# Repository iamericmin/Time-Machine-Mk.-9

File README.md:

# Time-Machine-Mk.-9
Time Machine Mk. 9

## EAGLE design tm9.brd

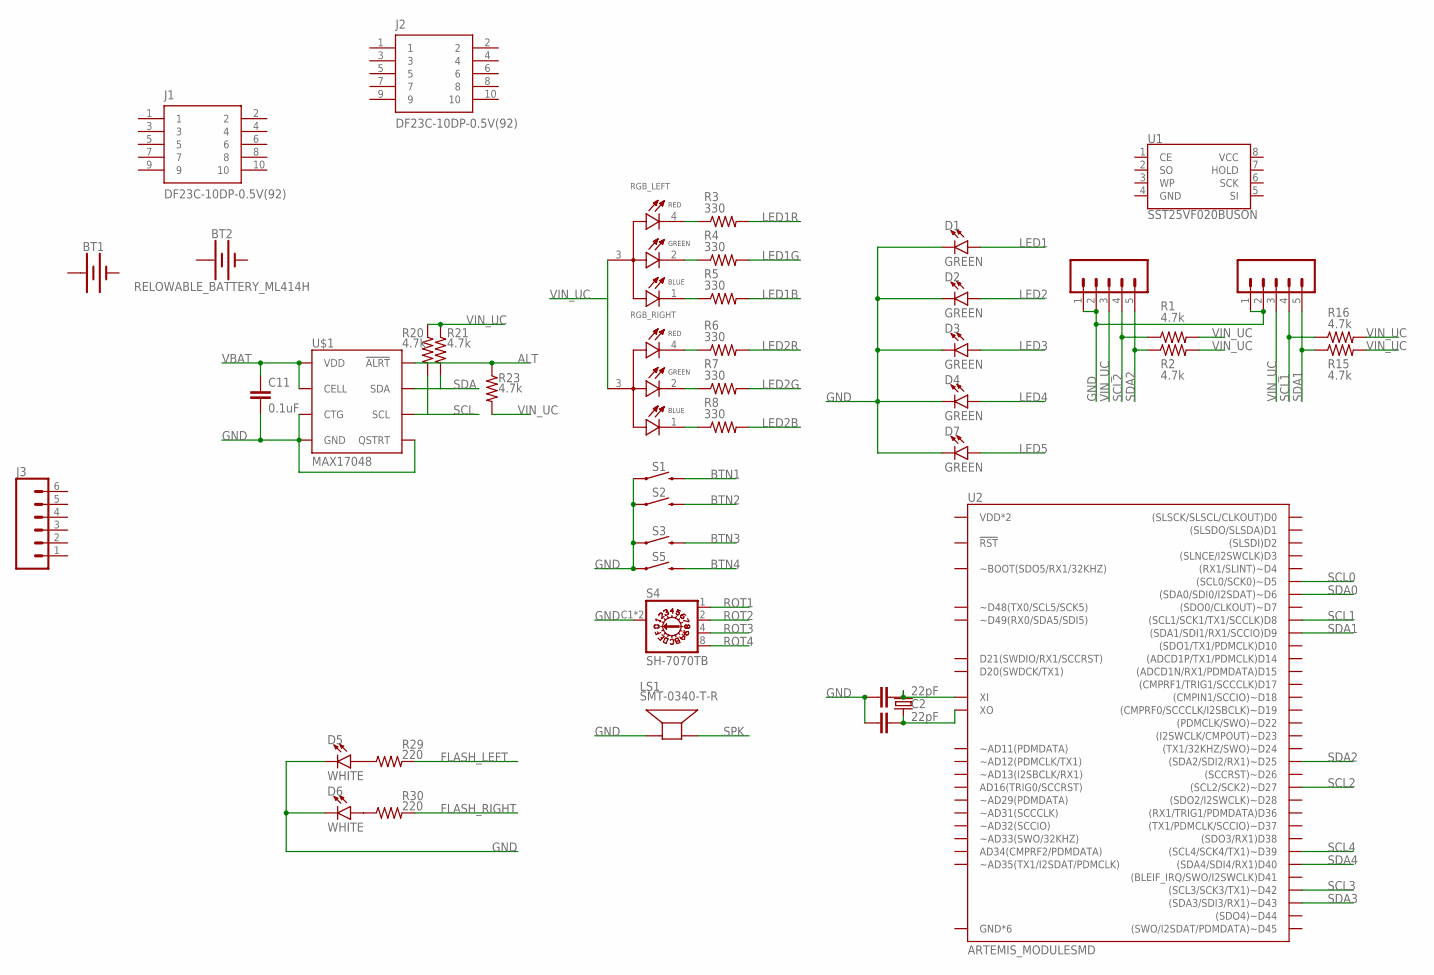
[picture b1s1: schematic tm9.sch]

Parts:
BT1: BATTERY-20MM_SMD_4LEGS_OVERPASTE_INNER; BATTCON_20MM_4LEGS_OVERPASTE_INNER
BT2: RELOWABLE_BATTERY_ML414H; ML414H_IV01E
C1, C2: 22pF; C0402
C11: 0.1uF; C0402
D1, D2, D3, D4, D7: GREEN; LED-1206
D5, D6: WHITE; LED-1206
J1, J2: DF23C-10DP-0.5V(92); HIROSE_DF23C-10DP-0.5V(92)
J3: CONN_06JST-SMD-LOCKING; JST-6-SMD-1.25MM-LOCKING
LCD1, LCD2: CONN_05VERT_FEMALE_HEADER; 1X05_SMD_VERTICAL_COMBO
LS1: SMT-0340-T-R; XDCR_SMT-0340-T-R
R1, R2, R15, R16, R20, R21, R23: 4.7k; R0402
R3, R4, R5, R6, R7, R8: 330; R0402
R29, R30: 220; R0402
RGB_LEFT: EAST1616RGBA3; LED_EAST1616RGBA3
RGB_RIGHT: EAST1616RGBA3; LED_EAST1616RGBA3
S1, S2, S3, S5: MOMENTARY-SWITCH-SPST-SMD-6.0X3.5MM; TACTILE_SWITCH_SMD_6.0X3.5MM
S4: SH-7070TB; SH-7070B
U1: SST25VF020BUSON; USON_3X2MM
U2: ARTEMIS_MODULESMD; ARTEMIS_FP
U$1: MAX17048; DFN-8
Y1: 32.768kHz; CRYSTAL-SMD-3.2X1.5MM

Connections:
+: BT1.1 (+), BT2.+
-: BT1.2 (-), BT2.-
ALT: R23.1, U$1.P$5 (!ALRT)
BTN1: S1.2
BTN2: S2.2
BTN3: S3.2
BTN4: S5.2
FLASH_LEFT: R29.2
FLASH_RIGHT: R30.2
GND: C1.1, C2.1, C11.2, D1.C, D2.C, D3.C, D4.C, D5.C, D6.C, D7.C, LCD1.1, LCD1.2, LCD2.1, LCD2.2, LS1.P, S1.1, S2.1, S3.1, S4.C1 (C), S4.C2 (C), S5.1, U1.4 (GND), U$1.P$1 (CTG), U$1.P$4 (GND), U$1.P$6 (QSTRT), U$1.P$9 (GND)
LED1: D1.A
LED1B: R5.2
LED1G: R4.2
LED1R: R3.2
LED2: D2.A
LED2B: R8.2
LED2G: R7.2
LED2R: R6.2
LED3: D3.A
LED4: D4.A
LED5: D7.A
unnamed: R3.1, RGB_LEFT.4 (R_C)
unnamed: R4.1, RGB_LEFT.2 (G_C)
unnamed: R5.1, RGB_LEFT.1 (B_C)
unnamed: R6.1, RGB_RIGHT.4 (R_C)
unnamed: R7.1, RGB_RIGHT.2 (G_C)
unnamed: R8.1, RGB_RIGHT.1 (B_C)
unnamed: D5.A, R29.1
unnamed: D6.A, R30.1
ROT1: S4.1
ROT2: S4.2
ROT3: S4.4
ROT4: S4.8
SCL: R20.2, U$1.P$7 (SCL)
SCL0: U2.~D5 ((SCL0/SCK0)~D5)
SCL1: LCD2.4, R16.1, U2.D8 ((SCL1/SCK1/TX1/SCCLK)D8)
SCL2: LCD1.4, R1.1, U2.~D27 ((SCL2/SCK2)~D27)
SCL3: U2.~D42 ((SCL3/SCK3/TX1)~D42)
SCL4: U2.~D39 ((SCL4/SCK4/TX1)~D39)
SDA: R21.2, U$1.P$8 (SDA)
SDA0: U2.~D6 ((SDA0/SDI0/I2SDAT)~D6)
SDA1: LCD2.5, R15.1, U2.D9 ((SDA1/SDI1/RX1/SCCIO)D9)
SDA2: LCD1.5, R2.1, U2.~D25 ((SDA2/SDI2/RX1)~D25)
SDA3: U2.~D43 ((SDA3/SDI3/RX1)~D43)
SDA4: U2.D40 ((SDA4/SDI4/RX1)D40)
SPK: LS1.N
VBAT: C11.1, U$1.P$2 (CELL), U$1.P$3 (VDD)
VCC: U1.8 (VCC)
VIN_UC: LCD1.3, LCD2.3, R1.2, R2.2, R15.2, R16.2, R20.1, R21.1, R23.2, RGB_LEFT.3 (A), RGB_RIGHT.3 (A)
XIN32: C1.2, U2.XI, Y1.P$2 (2)
XOUT32: C2.2, U2.XO, Y1.P$1 (1)

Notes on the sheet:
R29
R30
R23
R20
R21

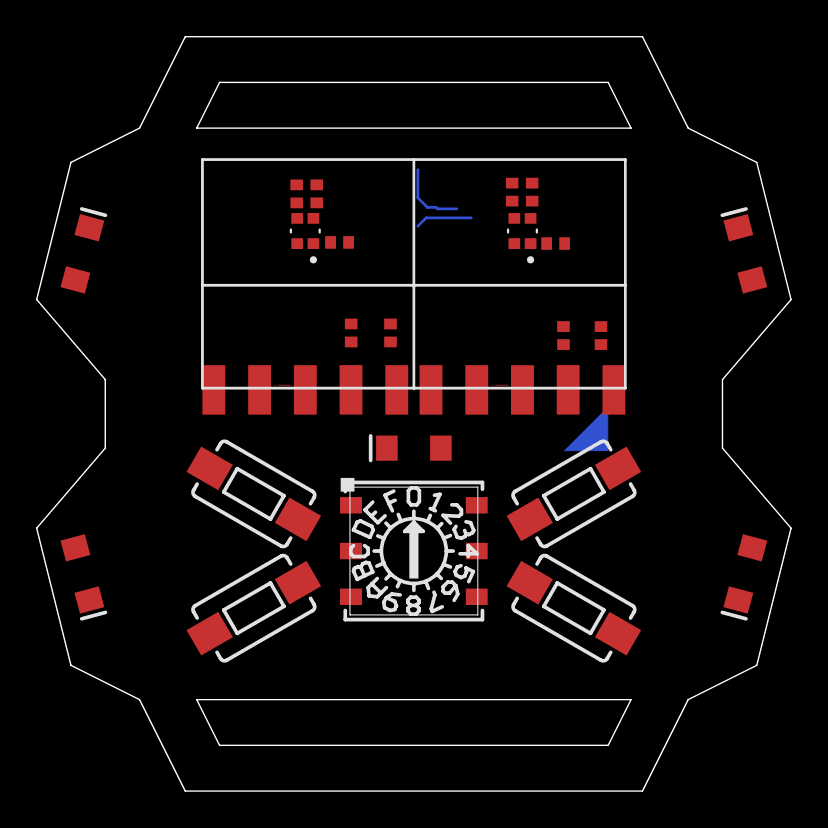
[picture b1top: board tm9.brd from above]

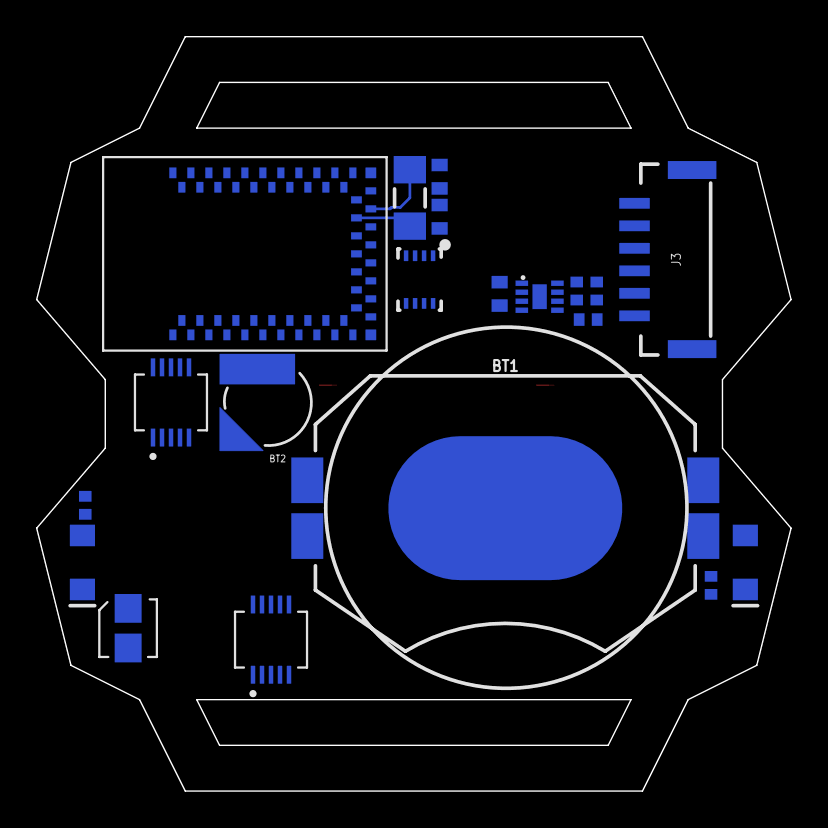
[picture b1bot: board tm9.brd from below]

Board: 2 copper layers, 41.9 x 41.9 mm, 44 parts (20 on the bottom side), 22 nets.

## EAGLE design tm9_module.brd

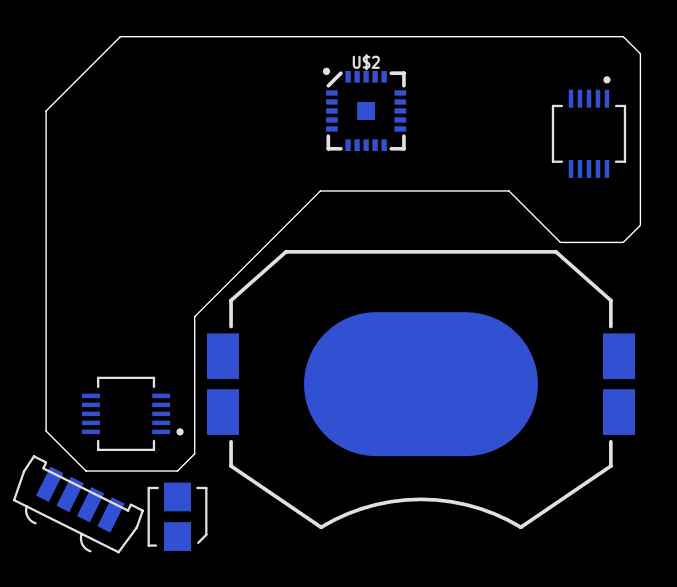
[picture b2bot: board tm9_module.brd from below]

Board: 2 copper layers, 33.0 x 24.1 mm, 6 parts (6 on the bottom side), 2 nets, no tracks yet.

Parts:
BT1: BATTCON_20MM_4LEGS_OVERPASTE_INNER
J1, J2: DF23C-10DP-0.5V(92); HIROSE_DF23C-10DP-0.5V(92)
LS1: SMT-0340-T-R; XDCR_SMT-0340-T-R
U$1: TSOP75238
U$2: NRF24L01SMD; QFN20-4X4MM

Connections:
VDD: U$2.7, U$2.15, U$2.18
VSS: U$2.0, U$2.8, U$2.14, U$2.17, U$2.20

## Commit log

2023-03-27 first commit!
2023-03-27 rough draft
    added JST-SH 6-pin RA connector, 1mA battery, and just shuffled around parts to get a general feel for things. Just a very rough draft.
2023-03-27 added SCL and SDA labels
    added SCL and SDA labels for all I2C ports on Artemis module.
    labeled both I2C LCDs accordingly for shortest I2C trace length.

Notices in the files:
parts and their libraries:
SparkFun-LED: Licensing: Creative Commons ShareAlike 4.0 International - https://creativecommons.org/licenses/by-sa/4.0
